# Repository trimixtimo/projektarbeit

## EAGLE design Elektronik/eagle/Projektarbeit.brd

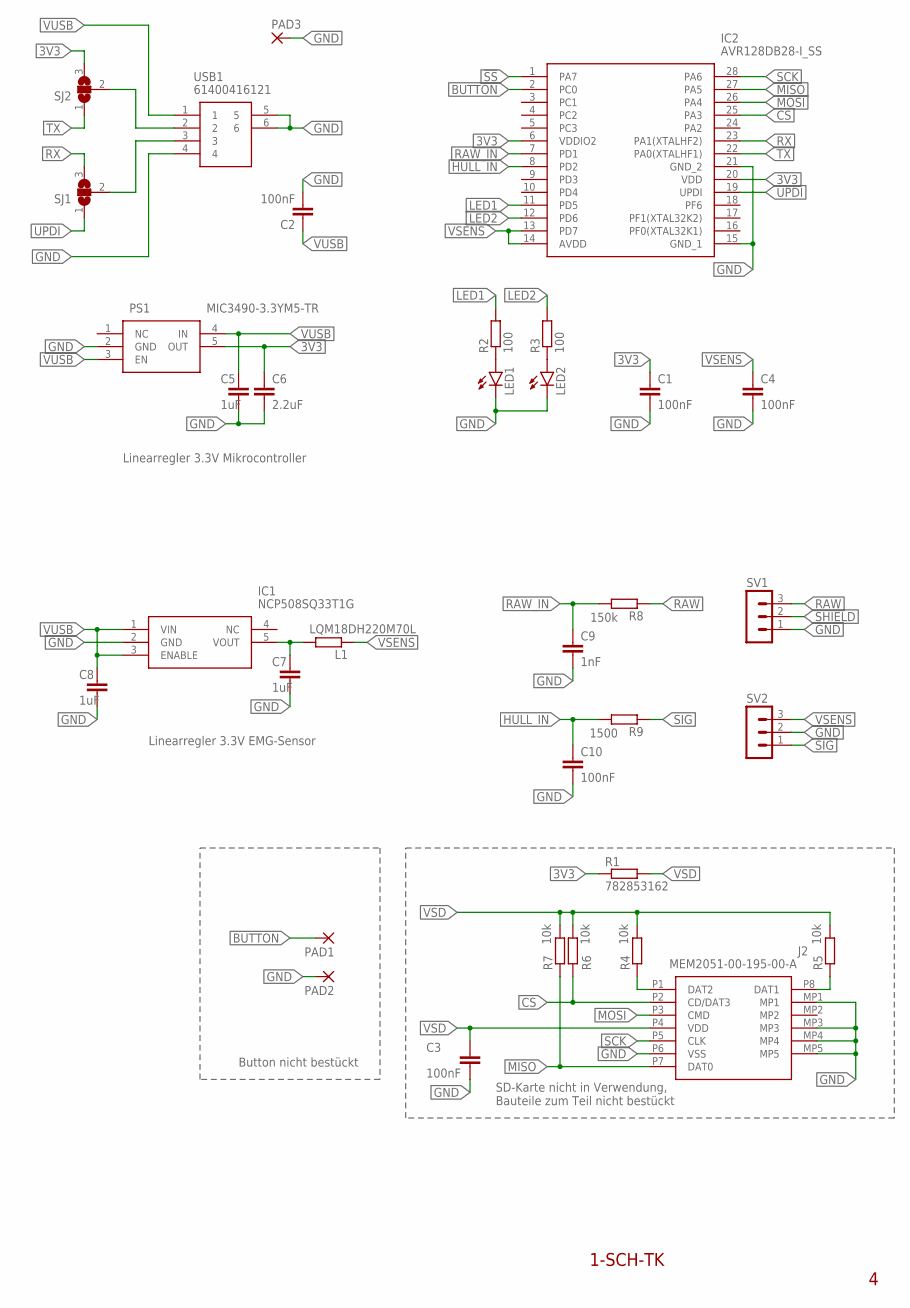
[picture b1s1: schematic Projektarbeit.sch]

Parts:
C1, C2, C3, C4, C10: 100nF; C0603
C5, C7, C8: 1uF; C0603
C6: 2.2uF; C0603
C9: 1nF; C0603
IC1: NCP508SQ33T1G; SOT65P210X110-5N
IC2: AVR128DB28-I_SS; SOP65P780X200-28N
J2: MEM2051-00-195-00-A; MEM20510019500A
L1: LQM18DH220M70L; R0603
LED1, LED2: LEDCHIPLED_0805; CHIPLED_0805
PAD1, PAD2: 2,15/1,0
PAD3: 2,54/0,9
PS1: MIC3490-3.3YM5-TR; SOT95P280X145-5N
R1: 782853162; R0805
R2, R3: 100; R0603
R4, R5, R6, R7: 10k; R0603
R8: 150k; R0603
R9: 1500; R0603
SJ1, SJ2: SJ2W; SJ_2
SV1, SV2: MA03-1
USB1: 61400416121

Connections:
3V3: C1.1, C6.1, IC2.6 (VDDIO2), IC2.20 (VDD), PS1.5 (OUT), R1.1, SJ2.3
!SS: IC2.1 (PA7)
BUTTON: IC2.2 (PC0), PAD1.1
CS: IC2.25 (PA3), J2.P2 (CD/DAT3), R6.1
GND: C1.2, C2.2, C3.2, C4.2, C5.2, C6.2, C7.2, C8.2, C9.2, C10.2, IC1.2 (GND), IC2.15 (GND_1), IC2.21 (GND_2), J2.MP1, J2.MP3, J2.MP4, J2.MP5, J2.P6 (VSS), LED1.C, LED2.C, PAD2.1, PAD3.1, PS1.2 (GND), SV1.1, SV2.2, USB1.4, USB1.5, USB1.6
HULL_IN: C10.1, IC2.8 (PD2), R9.2
LED1: IC2.11 (PD5), R2.2
LED2: IC2.12 (PD6), R3.2
MISO: IC2.27 (PA5), J2.P7 (DAT0), R7.1
MOSI: IC2.26 (PA4), J2.P3 (CMD)
unnamed: SJ1.2, USB1.3
unnamed: SJ2.2, USB1.2
unnamed: C7.1, IC1.5 (VOUT), L1.2
unnamed: LED1.A, R2.1
unnamed: J2.P1 (DAT2), R4.1
unnamed: J2.P8 (DAT1), R5.1
unnamed: LED2.A, R3.1
RAW: R8.1, SV1.3
RAW_IN: C9.1, IC2.7 (PD1), R8.2
RX: IC2.23 (PA1(XTALHF2)), SJ1.3
SCK: IC2.28 (PA6), J2.P5 (CLK)
SHIELD: SV1.2
SIG: R9.1, SV2.1
TX: IC2.22 (PA0(XTALHF1)), SJ2.1
UPDI: IC2.19 (UPDI), SJ1.1
VSD: C3.1, J2.P4 (VDD), R1.2, R4.2, R5.2, R6.2, R7.2
VSENS: C4.1, IC2.13 (PD7), IC2.14 (AVDD), L1.1, SV2.3
VUSB: C2.1, C5.1, C8.1, IC1.1 (VIN), IC1.3 (ENABLE), PS1.3 (EN), PS1.4 (IN), USB1.1

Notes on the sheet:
SD-Karte nicht in Verwendung, Bauteile zum Teil nicht bestückt
Button nicht bestückt
Linearregler 3.3V EMG-Sensor
Linearregler 3.3V Mikrocontroller
1-SCH-TK

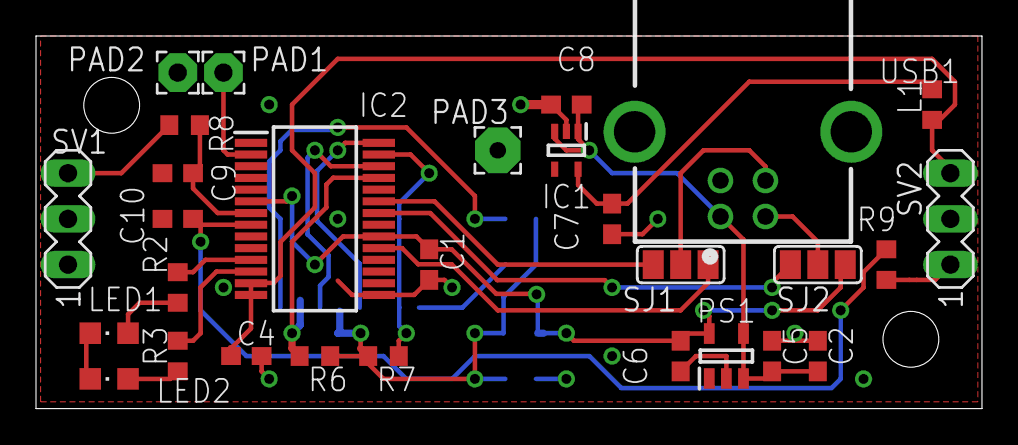
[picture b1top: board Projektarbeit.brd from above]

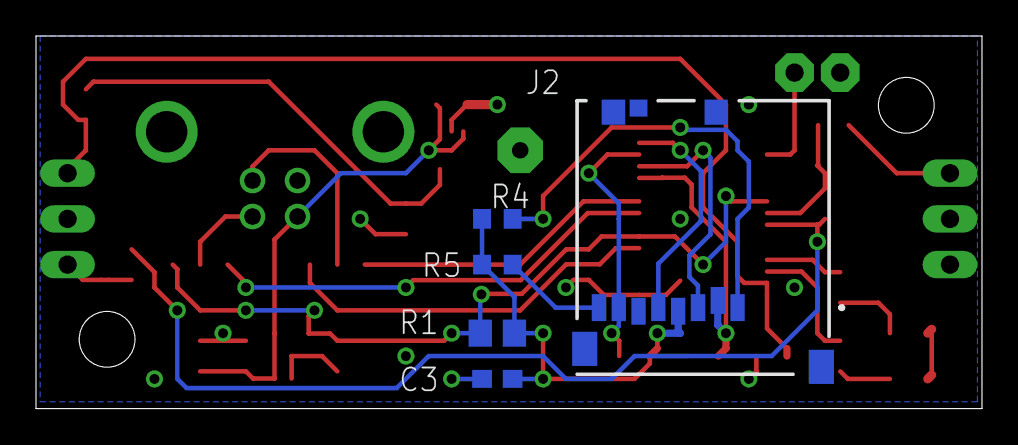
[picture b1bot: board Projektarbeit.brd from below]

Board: 2 copper layers, 52.6 x 20.7 mm, 34 parts (5 on the bottom side), 26 nets.

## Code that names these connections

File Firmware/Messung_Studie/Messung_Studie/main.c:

/*
 * SD_Messung.c
 *
 * Created: 01.04.2022 22:42:57
 * Author : Timo
 */ 

/*
 * A0 TX
 * A1 RX
 * A3 CS
 * A4 MOSI
 * A5 MISO
 * A6 SCK
 * A7 !SS
 * C0 Button
 * PD1 RAW_IN
 * PD2 HULL_IN
 * PD5 LED1 Grün
 * PD6 LED2 Blau
 * PD7 VSENSE
 */

#define F_CPU 16000000UL	//Takt 16MHz
#define periodendauer_us 100	//Abtastrate ADC in µs
#define baudrate_reg(baudrate) ((float)(F_CPU * 64 / (16 * (float)baudrate)))
#define baudrate 500000UL
#define uart0_maxstrlen 3
#define hull_cmd "hul"
#define raw_cmd "raw"
#define stop_cmd "stp"

#include <avr/io.h>
#include <util/delay.h>
#include <avr/cpufunc.h>
#include <avr/interrupt.h>
#include <stdbool.h>
#include <string.h>
#include <stdlib.h>
#include <stdint.h>

volatile uint16_t messwert = 0;	//globale, nicht von Optimierung erfasste Variable
volatile uint8_t uart0_str_count = 0;
char uart0_string[uart0_maxstrlen + 1] = "";

bool neuer_messwert = false;	//ungespeicherter Messwert vorhanden
bool messung_laeuft = 0;		//laufende Messung
bool cmd = 0;
uint16_t mode;
uint8_t hull;

void setup_io(void)
{
	PORTA_DIR = 0b01011001;	//SPI Interface Input/Output
	PORTC_DIR = 0b00000000;	//Alles Eingänge, Button an C0
	PORTD_DIR = 0b01100000;	//LED Outputs 5,6
	PORTC_PIN0CTRL = (1 << 3);	//Pullup für Button an C0
	PORTD_OUTSET = 0b01100000;	//beide LEDs an
}
void setup_vref(void)
{
	VREF_ADC0REF = VREF_ALWAYSON_bm | VREF_REFSEL_VREFA_gc;	//Referenzspannung immer an, externe Referenzspannung VREFA
}
void setup_adc(void)
{
	ADC0_CTRLA = (ADC_RUNSTBY_bm | ADC_FREERUN_bm);	//Freerunning Modus, Single Ended 12bit, kein Leftadjust, Runstandby	
	ADC0_CTRLC = ADC_PRESC_DIV32_gc;	//niedriger Takt für maximale Auflösung: 16 MHz / 32 = 500 kHz ADC Takt
	ADC0_MUXNEG = 0x40; //überflüssig, weil single-ended, nur zur Sicherheit
	ADC0_DBGCTRL = ADC_DBGRUN_bm;	//ADC debugging
	ADC0_SAMPCTRL = 0x10;		//Sample Dauer um 16 Takte verlängern -> geringere Belastung der Signalquelle
}
void setup_timer(void)
{
	TCA0_SINGLE_PER = periodendauer_us;
	TCA0_SINGLE_CTRLA = (TCA_SINGLE_RUNSTDBY_bm | (0x04 << 1) | TCA_SINGLE_ENABLE_bm);	//Prescaler 16: 16 MHz / 16 = 1 MHz
	TCA0_SINGLE_DBGCTRL = 0x01;	//debugging
	TCA0_SINGLE_INTCTRL = TCA_SINGLE_OVF_bm;	//Überlauf-Interrupt aktiviert	
}
void setup_uart(void)
{
	USART0.BAUD = (uint16_t) baudrate_reg(baudrate);	//set Baud rate
	USART0.CTRLC = USART_CMODE_ASYNCHRONOUS_gc | USART_PMODE_DISABLED_gc | USART_SBMODE_1BIT_gc | USART_CHSIZE_8BIT_gc;	//asynchron | no parity | 1 stop bit | 8 data bits
	USART0.CTRLA = USART_RXCIE_bm;	//enable receive interrupt
	USART0.DBGCTRL = USART_DBGRUN_bm;	//debugging mode
	USART0.CTRLB = USART_RXEN_bm |USART_TXEN_bm;	//uart rx und tx aktivieren
}

void uart0_sendChar(char c)
{
	while (!(USART0.STATUS & USART_DREIF_bm)){;}
	USART0.TXDATAL = c;
}
void uart0_sendString(char *str)
{
	for (uint8_t i = 0; i < strlen(str); i++)
	{
		uart0_sendChar(str[i]);
	}
}
void timer_start(void)
{
	TCA0_SINGLE_CTRLA |= TCA_SINGLE_ENABLE_bm;	//Timer starten
}
void timer_stop(void)
{
	cli();	//Interrupts unterdrücken
	TCA0_SINGLE_CTRLA &= ~TCA_SINGLE_ENABLE_bm;	//Timer stoppen
	TCA0_SINGLE_CNT = 0x00;	//Timer zurücksetzen
	sei();	//Interrupts wieder zulassen
}
void timer_reset (void)
{
	TCA0_SINGLE_CNT = 0x00;	//Timer zurücksetzen
}
void adc_channel_selection(void){
	ADC0_COMMAND = ADC_SPCONV_bm;	//Messung stoppen
	if (hull == 1)
	{
		ADC0_MUXPOS = 0x02; //für HULL-Input
	}
	else
	{
		ADC0_MUXPOS = 0x01; //für RAW-Input
	}
	_delay_ms(1);
	ADC0_CTRLA |= ADC_ENABLE_bm;	//ADC einschalten
	_delay_ms(1);
	ADC0_COMMAND = ADC_STCONV_bm;	//erste Messung starten
}
uint16_t adc_read(void)
{
	return ADC0_RES;
}
void wert_senden(uint16_t wert)
{
	char buffer[3];
	itoa(wert, buffer, 16);
	uart0_sendString(buffer);
	uart0_sendString("\n");
}

int main(void)
{
	CCP = CCP_IOREG_gc;	//geschützes Register entsperren
	CLKCTRL.OSCHFCTRLA = 0b10011101; //HF Clock Runstandby, 16 MHz CLK_Main, Autotune, CLK_PER = CLK_Main
	CPUINT.LVL1VEC = USART0_RXC_vect_num;
	
	setup_io();
	setup_vref();
	setup_adc();
	setup_timer();
	timer_stop();
	setup_uart();
	adc_channel_selection();
	
	sei();

	
	while(1)
	{
		/*PORTD_OUTSET = 0b01100000;	//grün
		_delay_ms(50);
		PORTD_OUTCLR = 0b01100000;	//blau aus
		_delay_ms(50);
		*/
	}
}

ISR(TCA0_OVF_vect)
{
	TCA0_SINGLE_INTFLAGS = 1; //löscht das Interrupt-Flag
	timer_reset();	//Timer wieder auf 0
	wert_senden(adc_read());
	neuer_messwert = 1;
}

ISR(USART0_RXC_vect)
{
	unsigned char nextChar;
	nextChar = USART0.RXDATAL;	//8 data bis, only use low register
	if (1 == 1) //if latest string got precessed completely
	{
		if (nextChar != '\n' && nextChar != '\r' && uart0_str_count < uart0_maxstrlen)	//save char if not end of line or max
		{
			uart0_string[uart0_str_count] = nextChar;
			uart0_str_count++;
		}
		else	//end of line or max length reached
		{
			uart0_str_count = 0;
			
			if (strcmp(uart0_string, hull_cmd) == 0)
			{
				hull = 1;
				adc_channel_selection();
				timer_start();	//Messung starten
				messung_laeuft = true;
				PORTD_OUTSET = 0b00100000;	//blau aus
				PORTD_OUTCLR = 0b01000000;	//grün an

			}
			if(strcmp(uart0_string, raw_cmd) == 0)
			{
				hull = 0;
				adc_channel_selection();
				timer_start();	//Messung starten
				messung_laeuft = true;
				PORTD_OUTSET = 0b01000000;	//blau an
				PORTD_OUTCLR = 0b00100000;	//grün aus
			}
			if(strcmp(uart0_string, stop_cmd) == 0)
			{
				neuer_messwert = 0;
				timer_stop();	//Messung stoppen
				messung_laeuft = false;
				PORTD_OUTSET = 0b01100000;	//beide LEDs an
			}			
		}
	}
}

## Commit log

2022-03-30 Push Datenblatt
2022-03-30 signaldateien für matlab
2022-03-30 Datenblatt ersetzt
2022-03-30 Datei zum Datenformat
2022-03-30 Firmware für Funktionstest
2022-03-30 Pinbelegung in Code kommentiert
2022-03-30 Eagle Files
2022-03-30 Portconfig
2022-03-30 Testprogramm blinkende LED fertiggestellt
2022-03-30 ADC Funktionen hinzugefügt
2022-03-30 Timer-Setup hinzugefügt
2022-03-31 Zeitkonstante integriert
2022-04-01 Arduino Code zum testen
2022-04-01 neue Messung mit 1ms Periodendauer bei Menu Hüllkurve
2022-04-01 Messung Meenu 1ms Periodendauer raw
2022-04-01 Verarbeitung mit Rohsignal
2022-04-01 Signal
2022-04-01 /Auswahl von Datei (uigetfile)
2022-04-01 /automatische Auswahl des Ordners 'Messungen'
2022-04-01 /Ordner erstellt
2022-04-01 / uigetfile(fullfile(...))
2022-04-01 funktionstüchtige LED-Firmware mit Reaktion auf Schalterstellung
2022-04-01 Neues Projekt für Hauptfirmware, LED Firmware auf notwendigsten Inhalt reduziert
2022-04-01 Alle vorhandenen Funktionen überprüft
2022-04-01 Funktionen zum starten und stoppen von TimerA0
2022-04-01 ISR für TimerA0 hinzugefügt
2022-04-01 ISR fertiggestellt
2022-04-01 Hauptfunktion geschrieben
2022-04-01 Änderungen der Register markiert
2022-04-05 FatFS Dateisystem Lib und Beispiele
2022-04-05 SD Spielwiese eingerichtet
2022-04-05 FatFs in Spielwiese integriert
2022-04-05 weiter SD KArten versuche
2022-04-05 SD_Messung in Messung_Studie umbenannt
2022-04-05 uart initialisierung
2022-04-05 Code umbau auf uart
2022-04-05 Fehler in main behoben, laufende messung wird nun gesetzt
2022-04-05 fertiger Code für Messung mit Schalter und Uart TX
2022-04-06 python
2022-04-06 TestCode für Serial
2022-04-06 Testmessung
2022-04-06 10Hz Messung
2022-04-06 Update Verarbeitung.m
    Umrechnung in mV variabel
2022-04-06 Messung real Linus
2022-04-06 Messungen hochladen
2022-04-07 Python Skript hinzugefügt
2022-04-08 code umgebaut auf variablen für hüll + leds
2022-04-08 Baudrate und Takt erhöht. Nun Messung mit 100us Abtastrate möglich
2022-04-08 Kommentare an neue Registerkonfiguration angepasst
2022-04-08 neue Registerkonfiguration in Datenblatt markiert
2022-04-08 ADC Takt und Sample-Dauer verlängert für bessere Ergebnisse
2022-04-08 Funktion für Umschalten zwischen Hull und Raw ergänzt
2022-04-08 starten und stoppen von Messungen über den PC, Umschalten von Raw zu Hull über den PC. Inklisove zwei Testmessungen mit den neuen Features und AMbu Elektroden
2022-04-10 Erste Messungen
2022-04-19 Neuer Python Code
2022-04-22 Python Code für Ansteuerung
2022-04-23 Schaltplan schick gemacht, Platinenansichten gedruckt
2022-04-23 veraltete Eagle Dateien gelöscht
2022-04-23 aktuelle Eagle Dateien in Elektronik abgelegt
2022-04-25 v0.1
2022-04-27 Änderungen an der Firmware
2022-04-29 Arbeit an der Firmware
2022-04-29 Messungen 29.04.
2022-05-01 Bilder für Vergleich angeglichen
2022-05-01 Größenvergleich Arduino vs AVR128
2022-05-01 MEssdaten und Simulation des Rohdaten Filters
2022-05-10 Studienmessungen
2022-05-10 Lokale Pfade aus M-Datei entfernt
2022-05-11 Messungen Melissa 200W
2022-05-11 Messungen Timo und Testmessungen
2022-05-11 Bilderupload
2022-05-16 Fehler in Messungen entfernt
2022-05-22 Bilder hinzugefügt
2022-05-30 Finale Matlab-Skripte hinzugefügt
